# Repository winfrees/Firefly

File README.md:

# Firefly

Small, cheap, solar-powered boards that live outdoors and talk to each other with light. Each board charges a supercapacitor during the day. At dusk it wakes up and flashes a red LED, and it watches for its neighbours' flashes with the same LED. Over time the boards fall into sync, like fireflies.

**Target:** about $5 per board, with a home 3D-printed case, an ordered PCB, and through-hole assembly at home.

## Status

Rev 0.1 is a draft. The schematic, BOM, a routed 50 × 36 mm two-layer PCB (passes DRC), an ISP programming jig and the firmware are done. The firmware passes all automated verification (unit tests, exhaustive two-board check, swarm simulation, and the real binary on a simulated ATtiny13A). Nothing has been built yet, so [bench validation](firmware/docs/bench-validation.md) is next.

## Hardware at a glance

| Block | Parts | Notes |
| --- | --- | --- |
| MCU | ATtiny13A, DIP-8, socketed | Runs from 1.8–5.5 V. A plain ATtiny13 needs ≥2.7 V |
| Power | 5 V 60 mA panel → BAT46 → 1 F 5.5 V supercap | No battery and no charging IC |
| Clamp | 5.6 V 1 W zener on the panel side | Holds the cap near 5.3 V; no drain at night |
| Light I/O | Red 5 mm water-clear LED between PB0 and PB1 | Drive it forward to flash; reverse-bias it to sense light |
| Sensing | Panel divider → PB2/ADC1, cap divider → PB3/ADC3 | Dusk detection and low-energy shutdown |
| Optional | Vibration switch on PB4 | Wakes the board on a tap or wind |

### Pin map

| Pin | Port | Job |
| --- | --- | --- |
| 1 | PB5 / RESET | 10k pull-up, kept as reset for ISP |
| 2 | PB3 / ADC3 | Cap voltage (3.9M / 1M divider) |
| 3 | PB4 | Optional tilt switch to GND |
| 4 | GND | Ground |
| 5 | PB0 | LED anode through 150 Ω |
| 6 | PB1 | LED cathode / sense input |
| 7 | PB2 / ADC1 | Panel voltage (100k / 22k divider) |
| 8 | VCC | VCAP rail, 100 nF at the pin |

### Rough energy budget (estimates, to be checked on the bench)

- Usable energy, 5.3 V → 1.8 V on 1 F: about 12 J
- Time to fill in full sun: about 1.5 min
- Run time flashing every 2.5 s: about 10–14 h ([firmware energy budget](firmware/docs/design.md#energy-budget))
- Run time asleep with no flashing: about 4 days

## Cost

About **$3.57 per board** for the parts you buy, or **$4.57** if you also buy the MCU. See [`hardware/bom.csv`](hardware/bom.csv). Prices are estimates for 20–50 boards, and the solar panel is the item most worth shopping around for.

## Files

| Path | What it is |
| --- | --- |
| `hardware/kicad/` | KiCad 7 project: `firefly.kicad_sch`, `firefly.kicad_pcb`, custom footprint library `firefly.pretty` |
| `hardware/fab/firefly-rev0.1-gerbers.zip` | Gerbers and drill files, ready to upload to JLCPCB, PCBWay or OSH Park |
| `hardware/fab/firefly-schematic.pdf` | Printable schematic |
| `hardware/images/` | Board renders and schematic images |
| `hardware/schematic.html` | Annotated schematic page with the pin map, energy budget and layout notes |
| `hardware/bom.csv` | Bill of materials |
| `hardware/kicad/design.py` | The part, net and placement list both the schematic and board are generated from |
| `firmware/` | ATtiny13A firmware, tests and docs: [README](firmware/README.md), [design](firmware/docs/design.md), [V&V report](firmware/docs/verification-report.md) |
| `hardware/isp-jig/` | Programming and power jig for the AVRISP mkII (KiCad project, Gerbers, BOM, how-to) |
| `tools/kicadgen/` | Scripts that turn a `design.py` into a KiCad schematic and routed board |

## PCB

- 50 × 36 mm, two layers, 1.6 mm FR-4, all through-hole, with two M3 mounting holes
- 0.4 mm tracks, 0.25 mm clearance, and a ground pour on both sides
- Autorouted with Freerouting; DRC passes with no errors and no unconnected pads
- Ordering: upload the Gerber zip and keep the fab's default settings (2 layers, 1.6 mm, HASL)

| Front | Back |
| --- | --- |
|  |  |

Opening it in KiCad: open `hardware/kicad/firefly.kicad_pro`. The footprints use KiCad's stock libraries, plus `firefly.pretty` for the supercap, which the project's `fp-lib-table` points to. The files were made with KiCad 7 and also open in KiCad 8 and 9.

Regenerating it: edit `hardware/kicad/design.py` and run the pipeline in [`tools/kicadgen`](tools/kicadgen/README.md).

## Assembly notes

- U1 is socketed and there is no ISP header, so program the chips on the [ISP jig](hardware/isp-jig/README.md) with an AVRISP mkII, then move them to the board. The LED sits between MOSI and MISO and C3 loads SCK, so in-circuit programming would be unreliable anyway.
- Fuses: 128 kHz or 1.2 MHz clock, BOD at 1.8 V, with BOD disabled during sleep in firmware.
- The internal 1.1 V reference is only accurate to ±10%, so calibrate ADC thresholds per board or leave margin.
- Outdoors: use a PETG or ASA case (not PLA), conformal-coat the board, and leave a drain hole under the panel.

## Roadmap

- [x] KiCad schematic and PCB (50 × 36 mm)
- [x] ISP programming and power jig for the AVRISP mkII
- [x] Firefly sync firmware (avr-gcc), with V&V documentation
- [ ] Bench validation on first boards ([procedure](firmware/docs/bench-validation.md))
- [ ] Enclosure STL

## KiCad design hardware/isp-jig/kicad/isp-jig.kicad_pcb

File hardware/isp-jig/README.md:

# ISP jig

A small through-hole board that holds an 8-pin AVR, powers it, and connects it to an **Atmel AVRISP mkII**. Each chip goes into the socket, gets flashed, and then moves to a firefly board.

## Why it exists

- **The AVRISP mkII doesn't power the chip.** It only senses the target's voltage, so this jig supplies power: USB 5 V through a resettable fuse, or anything from 1.8 to 5.5 V on J2. JP1 picks which.
- **The firefly board has no programming header.** On that board the LED sits across MOSI and MISO and a capacitor loads SCK, so the chips are programmed here instead.
- **You can test firmware on the bench.** D2 and R3 copy the firefly LED wiring (PB0 → 150 Ω → LED → PB1), so you can watch the flash and sense code work before a chip goes outside. J4 brings out all 8 pins for a scope or breadboard.

## Board

- 55 × 44 mm, two layers, all through-hole, two M3 holes
- DRC passes with no errors and no unconnected pads. The one warning is the USB socket's outline crossing the board edge, which is intentional: its mouth hangs over the edge.
- Gerbers: `fab/isp-jig-rev0.1-gerbers.zip`. Schematic: `fab/isp-jig-schematic.pdf`. Parts: `bom.csv` (about $0.80 in parts plus the PCB).

| Front | Back |
| --- | --- |
|  |  |

## Jumpers and connectors

| Part | Setting | What it does |
| --- | --- | --- |
| JP1 | 1-2 | Power the chip from USB 5 V (J1, through F1) |
| JP1 | 2-3 | Power the chip from J2 (1.8–5.5 V, e.g. 2×AA to mimic the supercap) |
| JP2 | fitted | Test LED connected, for running firmware |
| JP2 | open | **Required while programming.** The LED would load MOSI and MISO |
| J3 | — | AVRISP mkII 6-pin cable. The red stripe (pin 1) goes to the square pad |
| D1 | — | Lights when the chip has power |

## Using it with the AVRISP mkII

1. Set JP1 to USB and remove JP2.
2. Put the ATtiny13A in the socket with pin 1 (the dot) toward the notch.
3. Plug in USB power (D1 lights), then the mkII cable. The mkII's status LED turns green when it sees target power.
4. Check the connection:

   ```sh
   avrdude -c avrispmkII -P usb -p t13 -B 8
   ```

   It should print the signature `0x1e9007`.

5. Flash:

   ```sh
   avrdude -c avrispmkII -P usb -p t13 -B 8 -U flash:w:firefly.hex:i
   # or, from firmware/:  make flash
   ```

6. To test the firmware on the jig, fit JP2. The jig has no panel or supercap, so set the two sense pins on J4 with resistors: 10 kΩ from pin 2 to pin 8 (supercap OK) and 10 kΩ from pin 7 to pin 4 (night), or to pin 8 (day). The red LED then runs as it would on a firefly board. Without the resistors those pins float and the mode is unpredictable.

**Programming speed.** `-B` sets the programming clock period in microseconds. It has to stay slower than a quarter of the chip's clock:

| Chip clock | Use |
| --- | --- |
| 1.2 MHz (factory default) | `-B 8` or slower |
| 128 kHz (firefly low-power setting) | `-B 64` or slower |

If a chip stops answering right after a fuse change, it has usually just been slowed down. Retry with a bigger `-B`.

**Drivers.** On macOS and Linux avrdude finds the mkII as is (on Linux you may need a udev rule or `sudo`). On Windows, use Zadig to install the WinUSB or libusb-win32 driver for "AVRISP mkII", because avrdude can't use Atmel's old Jungo driver.

**Arduino IDE.** Install the MicroCore board package, select ATtiny13, and set the programmer to "AVRISP mkII". Then use *Burn Bootloader* (this only sets the fuses) and *Upload Using Programmer*.

## Regenerating

The schematic and board are generated from `kicad/design.py`. See [`tools/kicadgen`](../../tools/kicadgen/README.md).

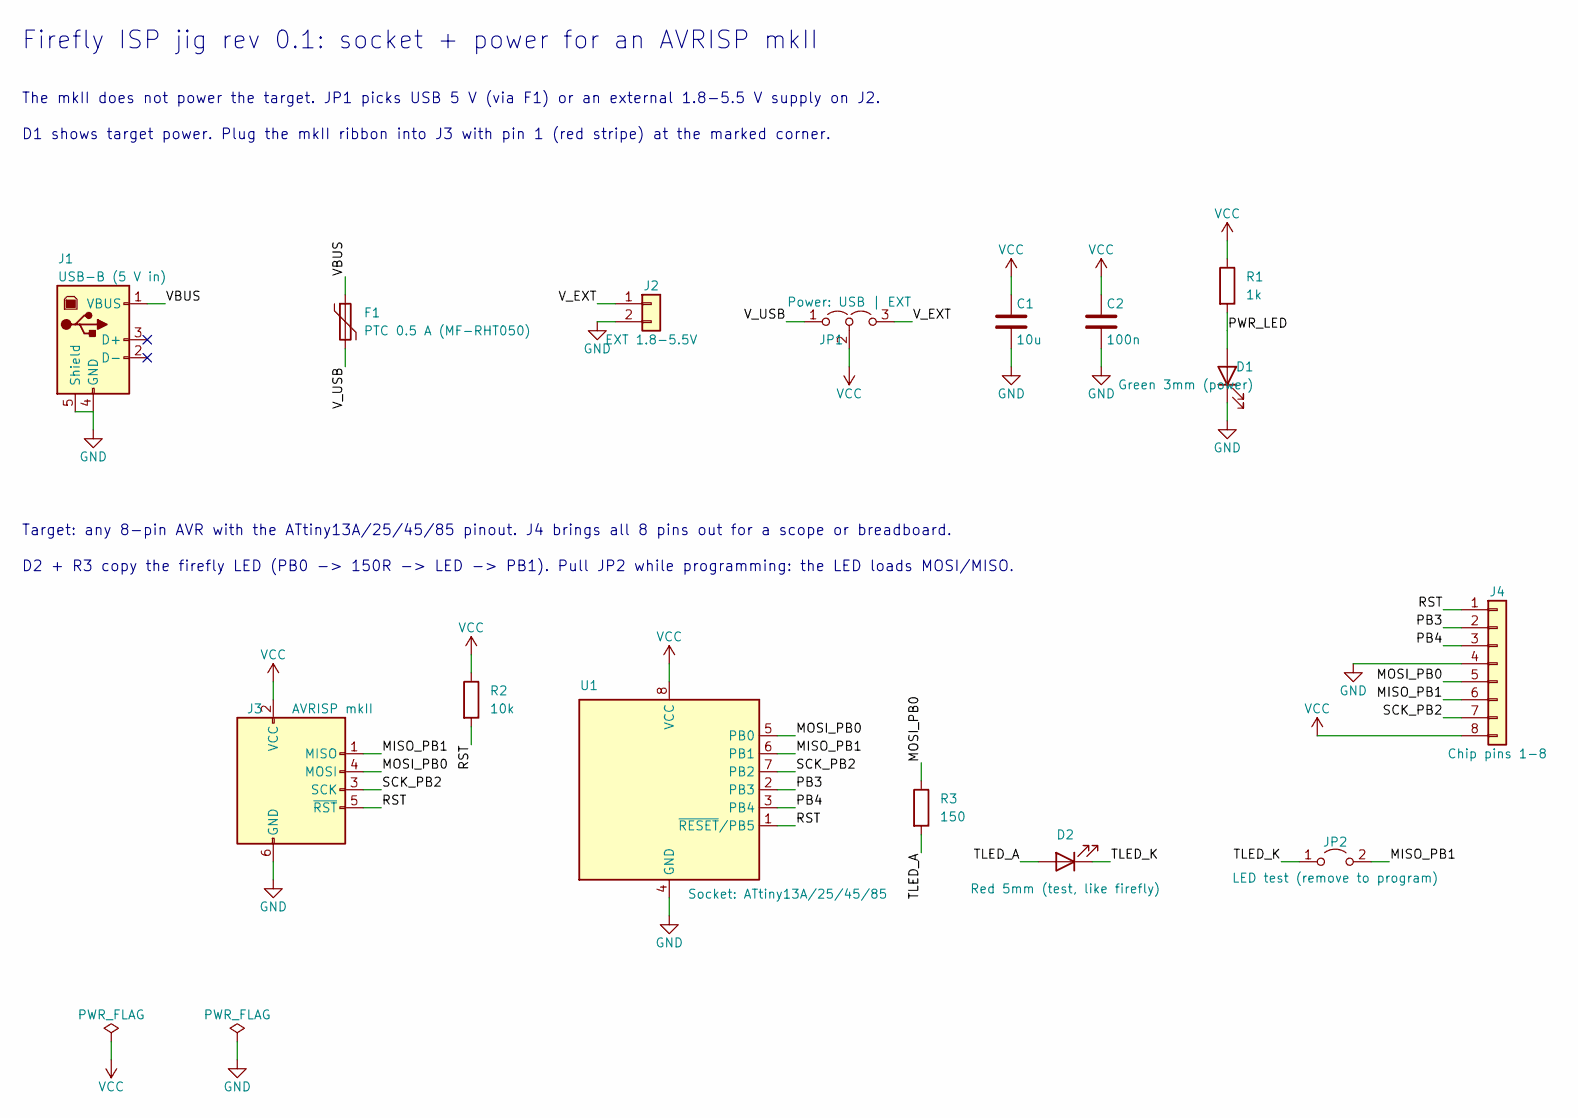
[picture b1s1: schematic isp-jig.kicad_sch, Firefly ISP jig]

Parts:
C1: 10u; C_Disc_D5.0mm_W2.5mm_P5.00mm
C2: 100n; C_Disc_D3.0mm_W2.0mm_P2.50mm
D1: Green 3mm (power); LED_D3.0mm
D2: Red 5mm (test, like firefly); LED_D5.0mm
F1: PTC 0.5 A (MF-RHT050); Fuse_Bourns_MF-RHT050
J1: USB-B (5 V in); USB_B_OST_USB-B1HSxx_Horizontal
J2: EXT 1.8-5.5V; PinHeader_1x02_P2.54mm_Vertical
J3: AVRISP mkII; PinHeader_2x03_P2.54mm_Vertical
J4: Chip pins 1-8; PinHeader_1x08_P2.54mm_Vertical
JP1: Power: USB | EXT; PinHeader_1x03_P2.54mm_Vertical
JP2: LED test (remove to program); PinHeader_1x02_P2.54mm_Vertical
R1: 1k; R_Axial_DIN0207_L6.3mm_D2.5mm_P7.62mm_Horizontal
R2: 10k; R_Axial_DIN0207_L6.3mm_D2.5mm_P7.62mm_Horizontal
R3: 150; R_Axial_DIN0207_L6.3mm_D2.5mm_P7.62mm_Horizontal
U1: Socket: ATtiny13A/25/45/85; DIP-8_W7.62mm_Socket

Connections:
GND: C1.2, C2.2, D1.1 (K), J1.4 (GND), J1.5 (Shield), J2.2, J3.6 (GND), J4.4, U1.4 (GND)
MISO_PB1: J3.1 (MISO), J4.6, JP2.2 (B), U1.6 (PB1)
MOSI_PB0: J3.4 (MOSI), J4.5, R3.1, U1.5 (PB0)
PB3: J4.2, U1.2 (PB3)
PB4: J4.3, U1.3 (PB4)
PWR_LED: D1.2 (A), R1.2
RST: J3.5 (~RST), J4.1, R2.2, U1.1 (~RESET/PB5)
SCK_PB2: J3.3 (SCK), J4.7, U1.7 (PB2)
TLED_A: D2.2 (A), R3.2
TLED_K: D2.1 (K), JP2.1 (A)
VBUS: F1.1, J1.1 (VBUS)
VCC: C1.1, C2.1, J3.2 (VCC), J4.8, JP1.2 (C), R1.1, R2.1, U1.8 (VCC)
V_EXT: J2.1, JP1.3 (B)
V_USB: F1.2, JP1.1 (A)

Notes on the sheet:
Firefly ISP jig rev 0.1: socket + power for an AVRISP mkII
The mkII does not power the target. JP1 picks USB 5 V (via F1) or an external 1.8-5.5 V supply on J2.
D1 shows target power. Plug the mkII ribbon into J3 with pin 1 (red stripe) at the marked corner.
Target: any 8-pin AVR with the ATtiny13A/25/45/85 pinout. J4 brings all 8 pins out for a scope or breadboard.
D2 + R3 copy the firefly LED (PB0 -> 150R -> LED -> PB1). Pull JP2 while programming: the LED loads MOSI/MISO.

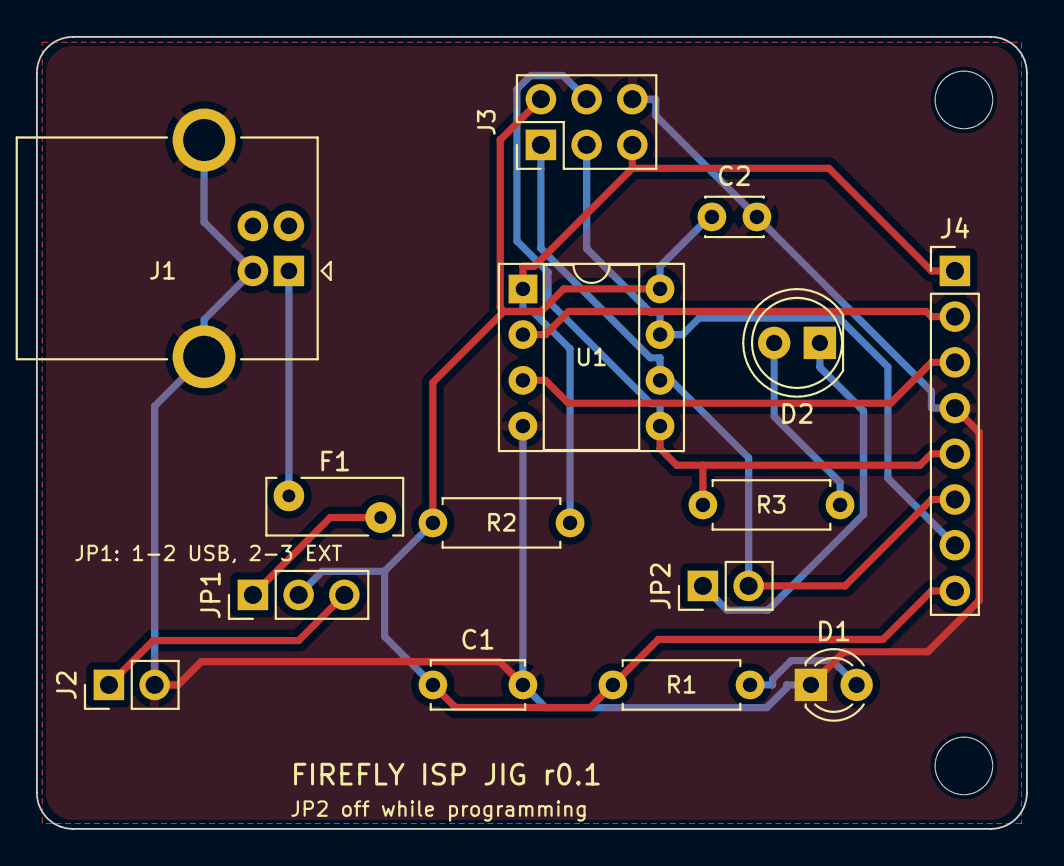
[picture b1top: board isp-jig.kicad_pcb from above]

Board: 2 copper layers, 55.0 x 44.0 mm, 17 parts (0 on the bottom side), 14 nets.

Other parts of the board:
H1, H2: MountingHole_3.2mm_M3

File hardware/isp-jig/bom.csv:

Ref,Part,Value/spec,Package,Qty,Unit USD (est.),Example part / source,Notes
J1,USB-B receptacle,"USB-B, right angle",THT,1,0.30,OST USB-B1HSxx or generic,Power only; data lines unused
F1,Resettable fuse,PTC 0.5 A hold,Radial 5.1 mm,1,0.15,Bourns MF-RHT050 or generic PTC,Protects the USB port from a shorted chip
J2,Pin header,1x02 2.54 mm,THT,1,0.02,Generic,External 1.8-5.5 V supply input
JP1,Pin header + shunt,1x03 2.54 mm,THT,1,0.03,Generic + 1 jumper shunt,Power select: 1-2 USB / 2-3 EXT
J3,Pin header,2x03 2.54 mm,THT,1,0.05,Generic (shrouded box header also fits),AVRISP mkII cable; red stripe to the square pad
U1,IC socket,8-pin DIP,DIP-8,1,0.03,Turned-pin socket,Holds the ATtiny13A being programmed
J4,Pin header,1x08 2.54 mm,THT,1,0.05,Generic,All 8 chip pins for scope or breadboard
JP2,Pin header + shunt,1x02 2.54 mm,THT,1,0.03,Generic + 1 jumper shunt,LED test: fit to try firmware; remove to program
C1,Capacitor,10 uF ceramic,Radial 5 mm,1,0.06,MLCC X5R 10 V,
C2,Capacitor,100 nF ceramic,Radial 2.54 mm,1,0.02,MLCC X7R 50 V,Right at U1
R1,Resistor,1k,Axial 1/4 W,1,0.01,Metal film,Power LED
R2,Resistor,10k,Axial 1/4 W,1,0.01,Metal film,RESET pull-up
R3,Resistor,150,Axial 1/4 W,1,0.01,Metal film,Same as firefly R1
D1,LED,Green 3 mm,THT,1,0.02,Generic,Target power on
D2,LED,Red 5 mm water-clear,THT,1,0.03,Generic,Same as firefly LED1
PCB,Circuit board,2-layer 55x44 mm,-,1,0.40,JLCPCB / PCBWay,Order alongside the firefly boards to share shipping

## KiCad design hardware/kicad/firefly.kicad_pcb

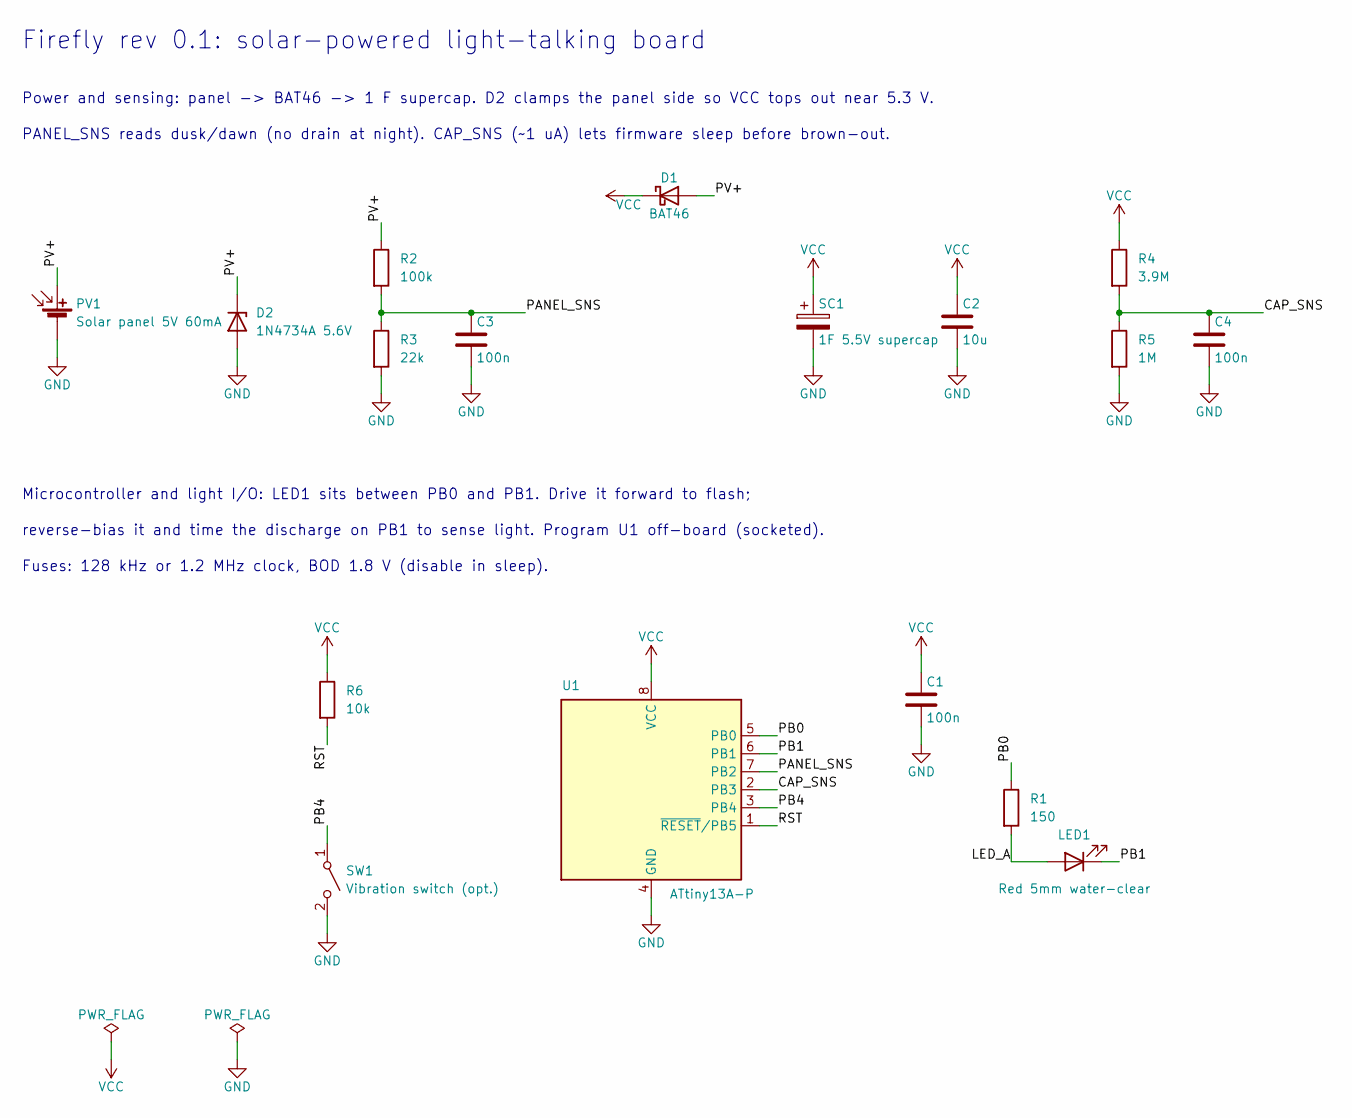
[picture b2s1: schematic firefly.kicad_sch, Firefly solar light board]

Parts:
C1, C3, C4: 100n; C_Disc_D3.0mm_W2.0mm_P2.50mm
C2: 10u; C_Disc_D5.0mm_W2.5mm_P5.00mm
D1: BAT46; D_DO-35_SOD27_P7.62mm_Horizontal
D2: 1N4734A 5.6V; D_DO-41_SOD81_P10.16mm_Horizontal
LED1: Red 5mm water-clear; LED_D5.0mm
PV1: Solar panel 5V 60mA; PinHeader_1x02_P2.54mm_Vertical
R1: 150; R_Axial_DIN0207_L6.3mm_D2.5mm_P7.62mm_Horizontal
R2: 100k; R_Axial_DIN0207_L6.3mm_D2.5mm_P7.62mm_Horizontal
R3: 22k; R_Axial_DIN0207_L6.3mm_D2.5mm_P7.62mm_Horizontal
R4: 3.9M; R_Axial_DIN0207_L6.3mm_D2.5mm_P7.62mm_Horizontal
R5: 1M; R_Axial_DIN0207_L6.3mm_D2.5mm_P7.62mm_Horizontal
R6: 10k; R_Axial_DIN0207_L6.3mm_D2.5mm_P7.62mm_Horizontal
SC1: 1F 5.5V supercap; SuperCap_Coin_Vertical_D19.2mm_W4.8mm_P5.00mm
SW1: Vibration switch (opt.); PinHeader_1x02_P2.54mm_Vertical
U1: ATtiny13A-P; DIP-8_W7.62mm_Socket

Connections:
CAP_SNS: C4.1, R4.2, R5.1, U1.2 (PB3)
GND: C1.2, C2.2, C3.2, C4.2, D2.2 (A), PV1.2 (-), R3.2, R5.2, SC1.2, SW1.2 (B), U1.4 (GND)
LED_A: LED1.2 (A), R1.2
PANEL_SNS: C3.1, R2.2, R3.1, U1.7 (PB2)
PB0: R1.1, U1.5 (PB0)
PB1: LED1.1 (K), U1.6 (PB1)
PB4: SW1.1 (A), U1.3 (PB4)
PV+: D1.2 (A), D2.1 (K), PV1.1 (+), R2.1
RST: R6.2, U1.1 (~RESET/PB5)
VCC: C1.1, C2.1, D1.1 (K), R4.1, R6.1, SC1.1, U1.8 (VCC)

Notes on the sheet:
Firefly rev 0.1: solar-powered light-talking board
Power and sensing: panel -> BAT46 -> 1 F supercap. D2 clamps the panel side so VCC tops out near 5.3 V.
PANEL_SNS reads dusk/dawn (no drain at night). CAP_SNS (~1 uA) lets firmware sleep before brown-out.
Microcontroller and light I/O: LED1 sits between PB0 and PB1. Drive it forward to flash;
reverse-bias it and time the discharge on PB1 to sense light. Program U1 off-board (socketed).
Fuses: 128 kHz or 1.2 MHz clock, BOD 1.8 V (disable in sleep).

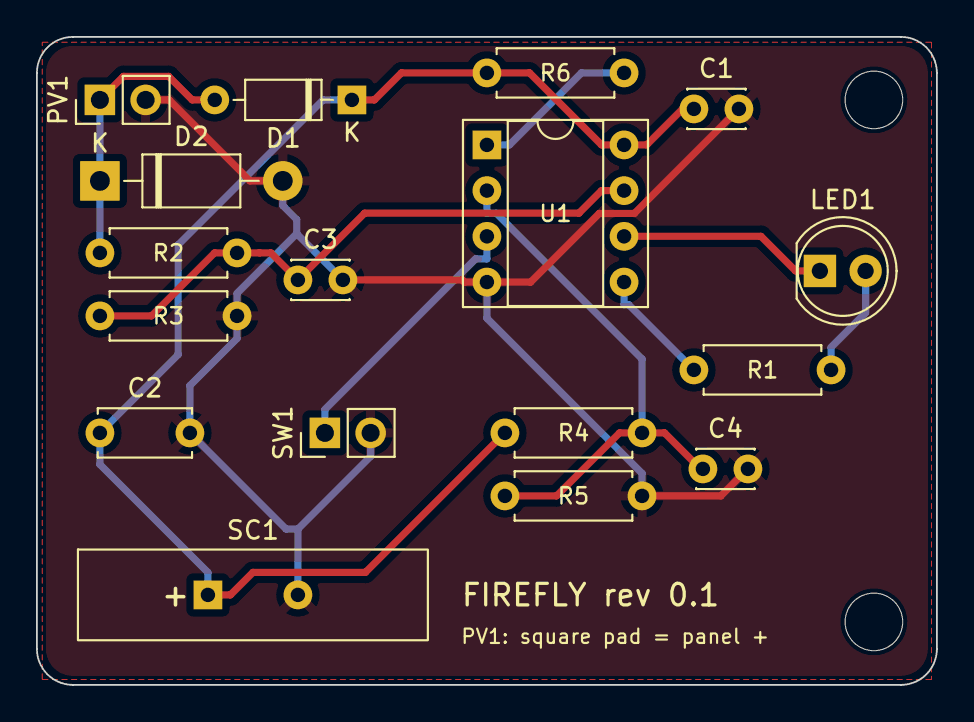
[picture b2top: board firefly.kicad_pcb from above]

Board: 2 copper layers, 50.0 x 36.0 mm, 19 parts (0 on the bottom side), 10 nets.

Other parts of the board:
H1, H2: MountingHole_3.2mm_M3

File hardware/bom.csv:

Ref,Part,Value/spec,Package,Qty,Unit USD (est.),Already own,Example part / source,Notes
U1,Microcontroller,ATtiny13A (1.8-5.5 V),DIP-8,1,1.0,yes,ATtiny13A-PU,Check marking: plain ATtiny13 needs >=2.7 V
XU1,IC socket,8-pin DIP,DIP-8,1,0.03,,Generic turned-pin,Program chips off-board
PV1,Solar panel,"5 V 60 mA (0.3 W), ~68x37 mm",Wire leads,1,1.5,,Generic epoxy mini panel,Biggest cost; US retail ~$1.90-3.60 each
SC1,Supercapacitor,1 F 5.5 V coin-stack,Radial 5 mm,1,0.95,,NIC NDLC105Z5.5V19.2X4.8VF / Eaton KR-5R5V105-R,ESR 15-30 ohm
D1,Schottky diode,BAT46 low leakage,DO-35,1,0.03,,BAT46 or BAT85,Avoid 1N5817 (leaky)
D2,Zener clamp,5.6 V 1 W,DO-41,1,0.03,,1N4734A,Panel side of D1; cap tops out ~5.3 V
LED1,LED flash+sense,5 mm red water-clear high-brightness,5 mm TH,1,0.03,,Generic 620-630 nm,Works from ~1.8 V
R1,Resistor,150 ohm,Axial 1/4 W,1,0.01,,Metal film 1%,LED current
R2,Resistor,100k,Axial 1/4 W,1,0.01,,Metal film 1%,Panel divider top
R3,Resistor,22k,Axial 1/4 W,1,0.01,,Metal film 1%,Panel divider bottom
R4,Resistor,3.9M,Axial 1/4 W,1,0.01,,Metal film 1%,Cap divider top (~1 uA)
R5,Resistor,1M,Axial 1/4 W,1,0.01,,Metal film 1%,Cap divider bottom
R6,Resistor,10k,Axial 1/4 W,1,0.01,,Metal film 1%,Reset pull-up
C1,Capacitor,100 nF ceramic,Radial 2.54 mm,1,0.02,,MLCC X7R 50 V,Decoupling at U1
C2,Capacitor,10 uF ceramic,Radial 5 mm,1,0.06,,MLCC X5R 10 V,LED pulse buffer
"C3,C4",Capacitor,100 nF ceramic,Radial 2.54 mm,2,0.02,,MLCC X7R 50 V,"ADC filter on PB2, PB3"
SW1,Vibration switch (optional),"Spring, normally open",TH,1,0.05,,SW-18010P,PB4 to GND
(PV1),Panel pads on PCB,2 pads 2.54 mm,Pads,1,0.0,,-,2-pin 2.54 mm footprint; solder panel leads or a header
PCB,Circuit board,2-layer ~35x35 mm 1.6 mm,-,1,0.4,,JLCPCB / PCBWay panelized,Shipping dominates small orders
ENC,Enclosure,PETG or ASA ~15 g,3D print,1,0.3,,Home printed,Not PLA outdoors
COAT,Weather protection,Conformal coating,-,1,0.05,,Acrylic coat / clear nail polish,Mask LED and socket
WIRE,Hookup wire,~10 cm 26 AWG,-,1,0.02,,Generic,Panel to J1

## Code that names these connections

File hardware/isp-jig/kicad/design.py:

"""Firefly ISP jig rev 0.1: socket + power board for an Atmel AVRISP mkII.

The mkII only senses target voltage, so this board powers the chip (USB 5 V
through a polyfuse, or an external 1.8-5.5 V supply picked with JP1). The
chip sits in an 8-pin socket wired to the standard 6-pin AVR ISP header.
D2 and R3 copy the firefly board's LED wiring (PB0 -> 150 R -> LED -> PB1)
so firmware can be tried on the bench; pull JP2 while programming.

Build with the scripts in tools/kicadgen (see tools/kicadgen/README.md).
"""

PROJECT = "isp-jig"
ROOT_UUID = "7c2e9a41-3b5d-4f60-8a71-2d3e4f5a6b7c"
TITLE = "Firefly ISP jig"
DATE = "2026-11-22"
REV = "0.1"
COMMENT = "Programming + power board for AVRISP mkII and 8-pin AVRs"

FP_R = "Resistor_THT:R_Axial_DIN0207_L6.3mm_D2.5mm_P7.62mm_Horizontal"
FP_C = "Capacitor_THT:C_Disc_D3.0mm_W2.0mm_P2.50mm"
H = "Connector_PinHeader_2.54mm:PinHeader_"

PARTS = [
    # ---- power -------------------------------------------------------
    dict(ref="J1", lib="Connector:USB_B", val="USB-B (5 V in)",
         fp="Connector_USB:USB_B_OST_USB-B1HSxx_Horizontal", sch=(35.56, 66.04, 0),
         skip={"5"}, pins={"1": "VBUS", "2": "NC", "3": "NC", "4": "GND", "5": "GND"},
         pcb=(14.0, 13.0, 180), ref_at=(-7.0, 0.0)),
    dict(ref="F1", lib="Device:Polyfuse", val="PTC 0.5 A (MF-RHT050)",
         fp="Fuse:Fuse_Bourns_MF-RHT050", sch=(71.12, 63.5, 0),
         pins={"1": "VBUS", "2": "V_USB"}, pcb=(14.0, 25.5, 0)),
    dict(ref="J2", lib="Connector_Generic:Conn_01x02", val="EXT 1.8-5.5V",
         fp=H + "1x02_P2.54mm_Vertical", sch=(114.3, 60.96, 0),
         pins={"1": "V_EXT", "2": "GND"}, pcb=(4.0, 36.0, 90)),
    dict(ref="JP1", lib="Jumper:Jumper_3_Open", val="Power: USB | EXT",
         fp=H + "1x03_P2.54mm_Vertical", sch=(142.24, 63.5, 0),
         pins={"1": "V_USB", "2": "VCC", "3": "V_EXT"}, pcb=(12.0, 31.0, 90)),
    dict(ref="C1", lib="Device:C", val="10u",
         fp="Capacitor_THT:C_Disc_D5.0mm_W2.5mm_P5.00mm", sch=(165.1, 63.5, 0),
         pins={"1": "VCC", "2": "GND"}, pcb=(22.0, 36.0, 0)),
    dict(ref="C2", lib="Device:C", val="100n",
         fp=FP_C, sch=(177.8, 63.5, 0), pins={"1": "VCC", "2": "GND"},
         pcb=(37.5, 10.0, 0)),
    dict(ref="R1", lib="Device:R", val="1k",
         fp=FP_R, sch=(195.58, 58.42, 0), skip={"2"}, pins={"1": "VCC", "2": "PWR_LED"},
         pcb=(32.0, 36.0, 0)),
    dict(ref="D1", lib="Device:LED", val="Green 3mm (power)",
         fp="LED_THT:LED_D3.0mm", sch=(195.58, 71.12, 90), skip={"2"},
         pins={"1": "GND", "2": "PWR_LED"}, pcb=(43.0, 36.0, 0), zone_full=True),
    # ---- target and ISP ------------------------------------------------
    dict(ref="U1", lib="MCU_Microchip_ATtiny:ATtiny13A-P",
         val="Socket: ATtiny13A/25/45/85", fp="Package_DIP:DIP-8_W7.62mm_Socket",
         sch=(116.84, 129.54, 0),
         pins={"1": "RST", "2": "PB3", "3": "PB4", "4": "GND",
               "5": "MOSI_PB0", "6": "MISO_PB1", "7": "SCK_PB2", "8": "VCC"},
         pcb=(27.0, 14.0, 0)),
    dict(ref="J3", lib="Connector:AVR-ISP-6", val="AVRISP mkII",
         fp=H + "2x03_P2.54mm_Vertical", sch=(63.5, 129.54, 0),
         pins={"1": "MISO_PB1", "2": "VCC", "3": "SCK_PB2", "4": "MOSI_PB0",
               "5": "RST", "6": "GND"}, pcb=(28.0, 6.0, 90), ref_at=(-3.0, -1.27)),
    dict(ref="R2", lib="Device:R", val="10k",
         fp=FP_R, sch=(88.9, 116.84, 0), pins={"1": "VCC", "2": "RST"},
         pcb=(22.0, 27.0, 0)),
    dict(ref="R3", lib="Device:R", val="150",
         fp=FP_R, sch=(152.4, 132.08, 0), pins={"1": "MOSI_PB0", "2": "TLED_A"},
         pcb=(37.0, 26.0, 0)),
    dict(ref="D2", lib="Device:LED", val="Red 5mm (test, like firefly)",
         fp="LED_THT:LED_D5.0mm", sch=(172.72, 139.7, 180),
         pins={"1": "TLED_K", "2": "TLED_A"}, pcb=(43.5, 17.0, 180)),
    dict(ref="JP2", lib="Jumper:Jumper_2_Open", val="LED test (remove to program)",
         fp=H + "1x02_P2.54mm_Vertical", sch=(210.82, 139.7, 0),
         pins={"1": "TLED_K", "2": "MISO_PB1"}, pcb=(37.0, 30.5, 90)),
    dict(ref="J4", lib="Connector_Generic:Conn_01x08", val="Chip pins 1-8",
         fp=H + "1x08_P2.54mm_Vertical", sch=(233.68, 111.76, 0), skip={"4", "8"},
         pins={"1": "RST", "2": "PB3", "3": "PB4", "4": "GND",
               "5": "MOSI_PB0", "6": "MISO_PB1", "7": "SCK_PB2", "8": "VCC"},
         pcb=(51.0, 13.0, 0)),
    # ---- ERC helpers ---------------------------------------------------
    dict(ref="#FLG01", lib="power:PWR_FLAG", val="PWR_FLAG", fp="",
         sch=(38.1, 165.1, 0), pins={"1": "VCC"}),
    dict(ref="#FLG02", lib="power:PWR_FLAG", val="PWR_FLAG", fp="",
         sch=(55.88, 165.1, 0), pins={"1": "GND"}),
]

SCH_WIRES = [(33.02, 76.2, 35.56, 76.2), (195.58, 62.23, 195.58, 64.77), (195.58, 64.77, 195.58, 67.31)]
SCH_WIRES += [(228.6, 111.76, 213.36, 111.76), (228.6, 121.92, 208.28, 121.92)]
SCH_POWER = [("GND", 213.36, 111.76, 0), ("VCC", 208.28, 121.92, 0)]
SCH_LABELS = [("PWR_LED", 195.58, 64.77, 0)]

NOTES = [
    ("Firefly ISP jig rev 0.1: socket + power for an AVRISP mkII", 25.4, 25.4, 2.5),
    ("The mkII does not power the target. JP1 picks USB 5 V (via F1) or an external 1.8-5.5 V supply on J2.", 25.4, 33.02, 1.5),
    ("D1 shows target power. Plug the mkII ribbon into J3 with pin 1 (red stripe) at the marked corner.", 25.4, 38.1, 1.5),
    ("Target: any 8-pin AVR with the ATtiny13A/25/45/85 pinout. J4 brings all 8 pins out for a scope or breadboard.", 25.4, 93.98, 1.5),
    ("D2 + R3 copy the firefly LED (PB0 -> 150R -> LED -> PB1). Pull JP2 while programming: the LED loads MOSI/MISO.", 25.4, 99.06, 1.5),
]

BOARD_W, BOARD_H = 55.0, 44.0
HOLES = [(51.5, 3.5), (51.5, 40.5)]
OVERHANG = {"J1"}  # USB socket mouth hangs over the left edge on purpose
SILK = [
    ("FIREFLY ISP JIG r0.1", 14.0, 41.0, 1.1, "F.SilkS"),
    ("JP2 off while programming", 14.0, 42.9, 0.8, "F.SilkS"),
    ("JP1: 1-2 USB, 2-3 EXT", 2.0, 28.7, 0.8, "F.SilkS"),
    ("github.com/winfrees/firefly", 14.0, 41.5, 0.9, "B.SilkS"),
]

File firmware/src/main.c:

/*
 * Firefly firmware for the ATtiny13A (board rev 0.1).
 *
 *   PB0  LED1 anode, through R1 150R   flash: drive high
 *   PB1  LED1 cathode                   flash: low; sense: reverse-charge, float
 *   PB2  ADC1  panel voltage (100k/22k)   day/night
 *   PB3  ADC3  supercap voltage (3.9M/1M) energy guard
 *   PB4  optional tilt/vibration switch to GND (internal pull-up)
 *   PB5  RESET (kept, for ISP)
 *
 * Everything runs from the watchdog: the chip sleeps in power-down and wakes
 * every 32 ms at night (8 s by day). Light is sensed with the LED itself:
 * charge its junction in reverse, float the cathode and let a pin-change
 * interrupt fire if light discharges it before the next tick. See
 * docs/design.md for the reasoning and docs/requirements.md for IDs.
 */
#include <avr/interrupt.h>
#include <avr/io.h>
#include <avr/sleep.h>
#include <avr/wdt.h>
#include <util/delay.h>

#include "config.h"
#include "firefly.h"

#define LED_A     PB0
#define LED_K     PB1
#define TAP       PB4
#define CH_PANEL  1          /* ADC1 = PB2 */
#define CH_CAP    3          /* ADC3 = PB3 */
#define LED_MASK  ((1 << LED_A) | (1 << LED_K))

#define WDT_32MS  (1 << WDP0)
#define WDT_8S    ((1 << WDP3) | (1 << WDP0))

enum { MODE_NIGHT, MODE_DAY, MODE_LOW };

static volatile uint8_t g_tick;    /* watchdog tick elapsed           */
static volatile uint8_t g_light;   /* LED discharged during this tick */
static volatile uint8_t g_tap;     /* tap switch closed               */
static uint8_t mode;

/* ---- interrupts ----------------------------------------------------- */

/* Marks a tick. WDTIE is cleared by hardware here and re-armed by the main
 * loop, so if the main loop ever hangs the next timeout resets the chip
 * (FW-SAFE-1). */
ISR(WDT_vect)
{
    g_tick = 1;
}

ISR(PCINT0_vect)
{
    uint8_t pins = PINB;
    if ((PCMSK & (1 << LED_K)) && !(pins & (1 << LED_K))) {
        g_light = 1;                         /* FW-SENSE-1 */
        PCMSK &= ~(1 << LED_K);
        DDRB |= (1 << LED_K);                /* hold low: no half-level input current */
    }
    if ((PCMSK & (1 << TAP)) && !(pins & (1 << TAP)))
        g_tap = 1;
}

/* ---- helpers -------------------------------------------------------- */

static void wdt_set(uint8_t wdp)
{
    cli();
    wdt_reset();
    WDTCR = (1 << WDCE) | (1 << WDE);
    WDTCR = (1 << WDTIE) | (1 << WDE) | wdp;  /* interrupt first, reset second */
    sei();
}

static void sleep_now(void)
{
    set_sleep_mode(SLEEP_MODE_PWR_DOWN);
    cli();
    sleep_enable();
#if defined(BODS) && defined(BODSE)
    sleep_bod_disable();                     /* FW-PWR-4 */
#endif
    sei();
    sleep_cpu();
    sleep_disable();
}

/* Average of 4 conversions against the 1.1 V bandgap; first one discarded. */
static uint16_t adc_read(uint8_t ch)
{
    uint16_t sum = 0;
    PRR &= ~(1 << PRADC);
    ADMUX = (1 << REFS0) | ch;
    ADCSRA = (1 << ADEN) | (1 << ADPS1) | (1 << ADPS0);   /* 1.2 MHz / 8 */
    for (uint8_t i = 0; i < 5; i++) {
        ADCSRA |= (1 << ADSC);
        while (ADCSRA & (1 << ADSC))
            ;
        if (i)
            sum += ADC;
    }
    ADCSRA = 0;
    PRR |= (1 << PRADC);                     /* FW-PWR-4 */
    return sum >> 2;
}

static void led_idle(void)
{
    PCMSK &= ~(1 << LED_K);
    PORTB &= ~LED_MASK;
    DDRB |= LED_MASK;                        /* both ends low: no bias */
}

static void flash(void)                      /* FW-LED-1 */
{
    PCMSK &= ~(1 << LED_K);
    DDRB |= LED_MASK;
    PORTB = (PORTB & ~(1 << LED_K)) | (1 << LED_A);
    _delay_ms(FLASH_MS);
    led_idle();
}

static void sense_arm(void)                  /* FW-SENSE-1 */
{
    /* Order matters: with the interrupt still enabled, making PB1 an output
     * while its PORT bit is 0 glitches it low and fakes a light event on
     * every tick (found in simulation, test IT-08). */
    PCMSK &= ~(1 << LED_K);
    PORTB = (PORTB & ~(1 << LED_A)) | (1 << LED_K);   /* K high first...     */
    DDRB |= LED_MASK;                                 /* ...then drive: reverse-charge */
    DDRB &= ~(1 << LED_K);                            /* float cathode...    */
    PORTB &= ~(1 << LED_K);                           /* ...with no pull-up  */
    GIFR = (1 << PCIF);
    PCMSK |= (1 << LED_K);
}

/* Decide day / night / low-energy from the panel and supercap (FW-PWR-1..3).
 * Bands between the thresholds keep the current mode (hysteresis). */
static void update_mode(void)
{
    uint16_t cap = adc_read(CH_CAP);
    uint16_t pan = adc_read(CH_PANEL);

    if (cap < ADC_CAP_LOW)
        mode = MODE_LOW;
    else if (mode == MODE_LOW && cap < ADC_CAP_RESUME)
        ;                                    /* still recovering */
    else if (pan > ADC_PANEL_DAY)
        mode = MODE_DAY;
    else if (pan < ADC_PANEL_NIGHT)
        mode = MODE_NIGHT;
    else if (mode == MODE_LOW)
        mode = MODE_DAY;                     /* recovered at twilight: wait */
}

/* ---- main ----------------------------------------------------------- */

int main(void)
{
    ff_state_t ff;
    uint8_t prev_light = 1;   /* no "edge" on the first tick */
    uint8_t measure = 0;
    uint8_t tap_hold = 0;

    MCUSR = 0;                               /* clear WDRF before touching WDE */
    wdt_disable();                           /* after a WDT reset it is still on (16 ms) */
    ACSR = (1 << ACD);                       /* analog comparator off */
    DIDR0 = (1 << ADC1D) | (1 << ADC3D);     /* no digital buffers on analog pins */
    PRR = (1 << PRTIM0) | (1 << PRADC);
    PORTB = (1 << TAP);                      /* pull-up on the tap switch */
    DDRB = LED_MASK;
    GIMSK = (1 << PCIE);
    PCMSK = (1 << TAP);
    sei();

    {
        uint16_t c = adc_read(CH_CAP);
        uint16_t p = adc_read(CH_PANEL);
        ff_init(&ff, (uint8_t)(c ^ (c >> 3) ^ (p << 2)));   /* FW-SYNC-4 */
        if (c >= ADC_CAP_RESUME)
            for (uint8_t i = 0; i < BOOT_FLASHES; i++) {    /* FW-LED-2 */
                flash();
                _delay_ms(150);
            }
    }
    mode = MODE_LOW;
    update_mode();
    /* The watchdog starts only now: the boot flashes take longer than two
     * timeouts and would otherwise reset the chip (found in simulation). */
    if (mode == MODE_NIGHT) {
        wdt_set(WDT_32MS);
        sense_arm();
    } else {
        wdt_set(WDT_8S);
    }

    for (;;) {
        sleep_now();

        cli();
        uint8_t tick = g_tick, tap = g_tap;
        g_tick = 0;
        g_tap = 0;
        sei();

        if (tap) {                           /* FW-TAP-1: react now, hold off rattles */
            PCMSK &= ~(1 << TAP);
            tap_hold = TAP_HOLDOFF_TICKS;
            if (mode == MODE_NIGHT) {
                ff_fire_now(&ff);
                flash();
                sense_arm();
            } else if (mode == MODE_DAY) {
                flash();                     /* FW-TAP-2: "I'm alive" */
            }
        }
        if (!tick)
            continue;                        /* a pin-change wake: not a tick */
        WDTCR |= (1 << WDTIE);               /* FW-SAFE-1: we are alive */

        cli();
        uint8_t light = g_light;
        g_light = 0;
        sei();

        if (mode == MODE_NIGHT) {
            /* FW-SENSE-2: count a flash only on dark -> light */
            uint8_t fire = ff_tick(&ff, light && !prev_light);
            prev_light = light;
            if (fire)
                flash();
            if (tap_hold && --tap_hold == 0)
                PCMSK |= (1 << TAP);
            if (++measure >= MEASURE_EVERY_TICKS) {
                measure = 0;
                update_mode();
            }
            if (mode == MODE_NIGHT) {
                sense_arm();
            } else {
                led_idle();
                wdt_set(WDT_8S);
            }
        } else {
            tap_hold = 0;                    /* a timed 8 s wake: taps allowed again */
            PCMSK |= (1 << TAP);
            update_mode();
            if (mode == MODE_NIGHT) {
                prev_light = 1;
                measure = 0;
                wdt_set(WDT_32MS);
                sense_arm();
            }
        }
    }
}

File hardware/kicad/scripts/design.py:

"""Single source of truth for the Firefly rev 0.1 board.

Both the schematic and the PCB are generated from this file, so they
always share the same parts, footprints and nets.
"""

FP_R = "Resistor_THT:R_Axial_DIN0207_L6.3mm_D2.5mm_P7.62mm_Horizontal"
FP_C = "Capacitor_THT:C_Disc_D3.0mm_W2.0mm_P2.50mm"
FP_C5 = "Capacitor_THT:C_Disc_D5.0mm_W2.5mm_P5.00mm"
FP_HDR2 = "Connector_PinHeader_2.54mm:PinHeader_1x02_P2.54mm_Vertical"

# ref, lib_id, value, footprint, sch (x, y, rot), pin -> net, pcb (x, y, rot)
# PCB coordinates are mm from the board's top-left corner.
PARTS = [
    # ---- power and sensing -------------------------------------------
    dict(ref="PV1", lib="Device:Solar_Cell", val="Solar panel 5V 60mA",
         fp=FP_HDR2, sch=(30.48, 63.5, 0), pins={"1": "PV+", "2": "GND"},
         pcb=(3.5, 3.5, 90), note="Panel leads solder here (+ is pin 1)"),
    dict(ref="D2", lib="Device:D_Zener", val="1N4734A 5.6V",
         fp="Diode_THT:D_DO-41_SOD81_P10.16mm_Horizontal", sch=(55.88, 63.5, 270),
         pins={"1": "PV+", "2": "GND"}, pcb=(3.5, 8.0, 0)),
    dict(ref="R2", lib="Device:R", val="100k",
         fp=FP_R, sch=(76.2, 55.88, 0), skip={"2"}, pins={"1": "PV+", "2": "PANEL_SNS"},
         pcb=(3.5, 12.0, 0)),
    dict(ref="R3", lib="Device:R", val="22k",
         fp=FP_R, sch=(76.2, 67.31, 0), skip={"1"}, pins={"1": "PANEL_SNS", "2": "GND"},
         pcb=(3.5, 15.5, 0)),
    dict(ref="C3", lib="Device:C", val="100n",
         fp=FP_C, sch=(88.9, 66.04, 0), skip={"1"}, pins={"1": "PANEL_SNS", "2": "GND"},
         pcb=(14.5, 13.5, 0)),
    dict(ref="D1", lib="Device:D_Schottky", val="BAT46",
         fp="Diode_THT:D_DO-35_SOD27_P7.62mm_Horizontal", sch=(116.84, 45.72, 0),
         pins={"1": "VCC", "2": "PV+"}, pcb=(17.5, 3.5, 180)),
    dict(ref="SC1", lib="Device:C_Polarized", val="1F 5.5V supercap",
         fp="firefly:SuperCap_Coin_Vertical_D19.2mm_W4.8mm_P5.00mm",
         sch=(137.16, 63.5, 0), pins={"1": "VCC", "2": "GND"}, pcb=(12.0, 31.0, 0)),
    dict(ref="C2", lib="Device:C", val="10u",
         fp=FP_C5, sch=(157.48, 63.5, 0), pins={"1": "VCC", "2": "GND"},
         pcb=(3.5, 22.0, 0)),
    dict(ref="R4", lib="Device:R", val="3.9M",
         fp=FP_R, sch=(180.34, 55.88, 0), skip={"2"}, pins={"1": "VCC", "2": "CAP_SNS"},
         pcb=(26.0, 22.0, 0)),
    dict(ref="R5", lib="Device:R", val="1M",
         fp=FP_R, sch=(180.34, 67.31, 0), skip={"1"}, pins={"1": "CAP_SNS", "2": "GND"},
         pcb=(26.0, 25.5, 0)),
    dict(ref="C4", lib="Device:C", val="100n",
         fp=FP_C, sch=(193.04, 66.04, 0), skip={"1"}, pins={"1": "CAP_SNS", "2": "GND"},
         pcb=(37.0, 24.0, 0)),
    # ---- microcontroller and light I/O -------------------------------
    dict(ref="U1", lib="MCU_Microchip_ATtiny:ATtiny13A-P", val="ATtiny13A-P",
         fp="Package_DIP:DIP-8_W7.62mm_Socket",
         sch=(114.3, 129.54, 0),
         pins={"1": "RST", "2": "CAP_SNS", "3": "PB4", "4": "GND",
               "5": "PB0", "6": "PB1", "7": "PANEL_SNS", "8": "VCC"},
         pcb=(25.0, 6.0, 0)),
    dict(ref="R6", lib="Device:R", val="10k",
         fp=FP_R, sch=(68.58, 116.84, 0), pins={"1": "VCC", "2": "RST"},
         pcb=(25.0, 2.0, 0)),
    dict(ref="C1", lib="Device:C", val="100n",
         fp=FP_C, sch=(152.4, 116.84, 0), pins={"1": "VCC", "2": "GND"},
         pcb=(36.5, 4.0, 0)),
    dict(ref="R1", lib="Device:R", val="150",
         fp=FP_R, sch=(165.1, 132.08, 0), skip={"2"}, pins={"1": "PB0", "2": "LED_A"},
         pcb=(36.5, 18.5, 0)),
    dict(ref="LED1", lib="Device:LED", val="Red 5mm water-clear",
         fp="LED_THT:LED_D5.0mm", sch=(173.99, 139.7, 180), skip={"2"},
         pins={"1": "PB1", "2": "LED_A"}, pcb=(43.5, 13.0, 0),
         note="Flashes and senses light"),
    dict(ref="SW1", lib="Switch:SW_SPST", val="Vibration switch (opt.)",
         fp=FP_HDR2, sch=(68.58, 142.24, 270), pins={"1": "PB4", "2": "GND"},
         pcb=(16.0, 22.0, 90), note="SW-18010P or tilt switch, optional"),
    # ---- ERC helpers (no footprint) ----------------------------------
    dict(ref="#FLG01", lib="power:PWR_FLAG", val="PWR_FLAG", fp="",
         sch=(38.1, 165.1, 0), pins={"1": "VCC"}),
    dict(ref="#FLG02", lib="power:PWR_FLAG", val="PWR_FLAG", fp="",
         sch=(55.88, 165.1, 0), pins={"1": "GND"}),
]

# Mounting holes (PCB only), mm from top-left.
HOLES = [(46.5, 3.5), (46.5, 32.5)]
BOARD_W, BOARD_H = 50.0, 36.0

POWER_NETS = {"VCC", "GND"}

# Hand-drawn schematic wiring where labels would collide: (x1, y1, x2, y2)
SCH_WIRES = [
    (76.2, 59.69, 76.2, 62.23), (76.2, 62.23, 76.2, 63.5), (76.2, 62.23, 88.9, 62.23), (88.9, 62.23, 96.52, 62.23),
    (180.34, 59.69, 180.34, 62.23), (180.34, 62.23, 180.34, 63.5), (180.34, 62.23, 193.04, 62.23), (193.04, 62.23, 200.66, 62.23),
    (165.1, 135.89, 165.1, 139.7), (165.1, 139.7, 170.18, 139.7),
]
SCH_LABELS = [("PANEL_SNS", 96.52, 62.23, 0), ("CAP_SNS", 200.66, 62.23, 0),
              ("LED_A", 165.1, 139.7, 180)]
SCH_JUNCTIONS = [(76.2, 62.23), (88.9, 62.23), (180.34, 62.23), (193.04, 62.23)]
